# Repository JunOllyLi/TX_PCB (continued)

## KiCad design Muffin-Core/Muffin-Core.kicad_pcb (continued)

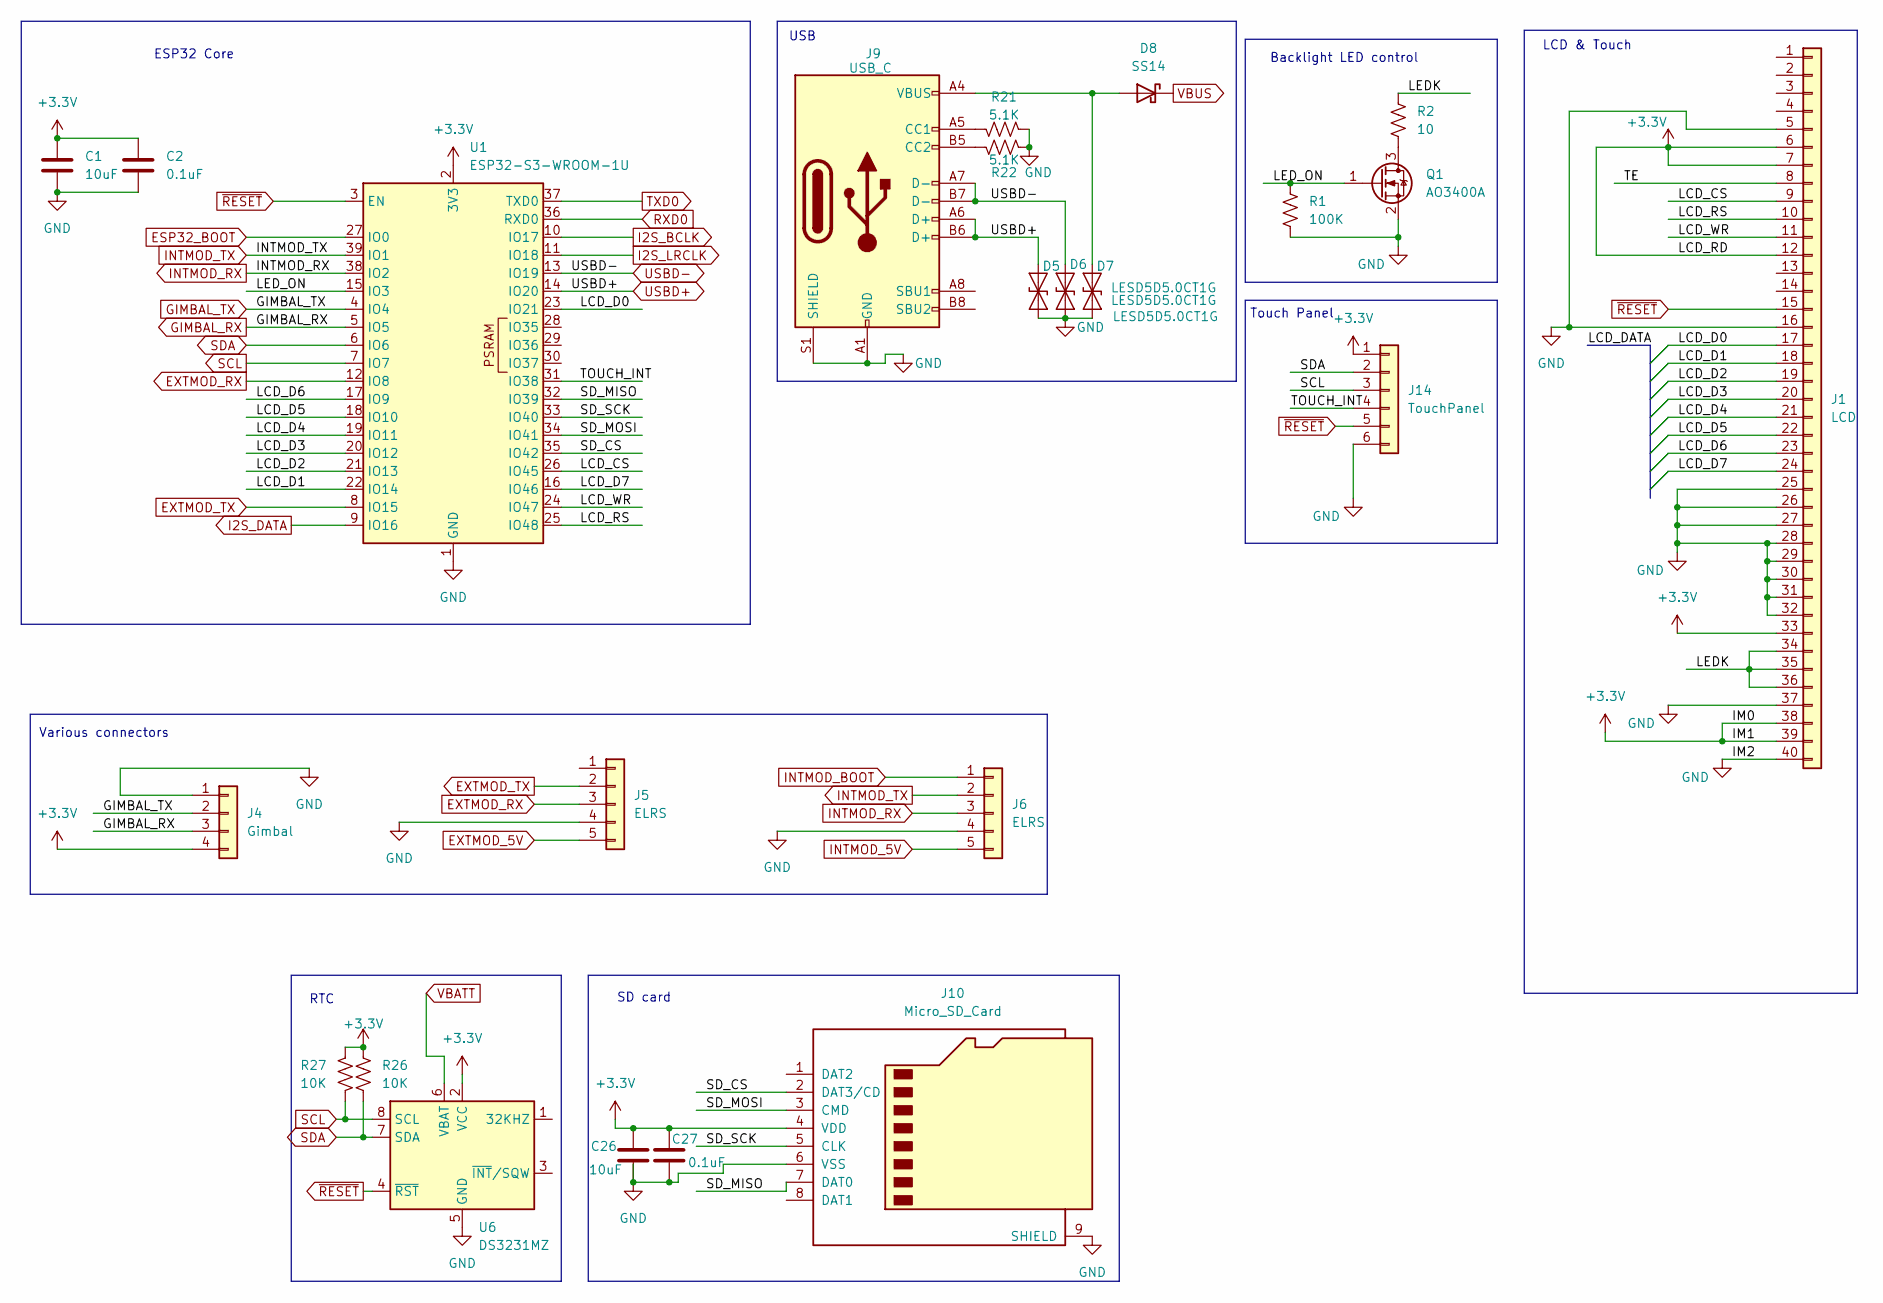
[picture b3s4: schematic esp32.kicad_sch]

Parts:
C1, C26: 10uF; C_0603_1608Metric_Pad1.08x0.95mm_HandSolder
C2, C27: 0.1uF; C_0603_1608Metric_Pad1.08x0.95mm_HandSolder
D5, D6, D7: LESD5D5.0CT1G; D_SOD-523
D8: SS14; D_SMA
J1: LCD; FPC_40PIN_TOP
J4: Gimbal; JST_ZH_B4B-ZR-SM4-TF_1x04-1MP_P1.50mm_Vertical
J5, J6: ELRS; Molex_PicoBlade_53398-0571_1x05-1MP_P1.25mm_Vertical
J9: USB_C; my_USB_C_Receptacle_GCT_USB4105-xx-A_16P_TopMnt_Horizontal
J10: Micro_SD_Card; MicroSD
J14: TouchPanel; FPC_6PIN_BOTTOM
Q1: AO3400A; SOT-23
R1: 100K; R_0603_1608Metric_Pad0.98x0.95mm_HandSolder
R2: 10; R_0603_1608Metric_Pad0.98x0.95mm_HandSolder
R21, R22: 5.1K; R_0603_1608Metric_Pad0.98x0.95mm_HandSolder
R26, R27: 10K; R_0603_1608Metric_Pad0.98x0.95mm_HandSolder
U1: ESP32-S3-WROOM-1U
U6: DS3231MZ; SOIC-8_3.9x4.9mm_P1.27mm

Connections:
+3.3V: C1.1, C2.1, C26.1, C27.1, J1.6, J1.7, J1.12, J1.33, J1.38, J1.39, J4.4, J10.4 (VDD), J14.1, R26.1, R27.1, U1.2 (3V3), U6.2 (VCC); also elsewhere on the board
/ESP32/LCD_CS: J1.9, U1.26 (IO45)
/ESP32/LCD_D0: J1.17, U1.23 (IO21)
/ESP32/LCD_D1: J1.18, U1.22 (IO14)
/ESP32/LCD_D2: J1.19, U1.21 (IO13)
/ESP32/LCD_D3: J1.20, U1.20 (IO12)
/ESP32/LCD_D4: J1.21, U1.19 (IO11)
/ESP32/LCD_D5: J1.22, U1.18 (IO10)
/ESP32/LCD_D6: J1.23, U1.17 (IO9)
/ESP32/LCD_D7: J1.24, U1.16 (IO46)
/ESP32/LCD_RS: J1.10, U1.25 (IO48)
/ESP32/LCD_WR: J1.11, U1.24 (IO47)
/ESP32/LEDK: J1.34, J1.35, J1.36, R2.1
/ESP32/LED_ON: Q1.1 (G), R1.1, U1.15 (IO3)
/ESP32/SD_CS: J10.2 (DAT3/CD), U1.35 (IO42)
/ESP32/SD_MISO: J10.7 (DAT0), U1.32 (IO39)
/ESP32/SD_MOSI: J10.3 (CMD), U1.34 (IO41)
/ESP32/SD_SCK: J10.5 (CLK), U1.33 (IO40)
/ESP32/TE: J1.8
/ESP32/TOUCH_INT: J14.4, U1.31 (IO38)
ESP32_BOOT: U1.27 (IO0); also elsewhere on the board
EXTMOD_5V: J5.5; also elsewhere on the board
EXTMOD_RX: J5.3, U1.12 (IO8); also elsewhere on the board
EXTMOD_TX: J5.2, U1.8 (IO15); also elsewhere on the board
GIMBAL_RX: J4.3, U1.5 (IO5)
GIMBAL_TX: J4.2, U1.4 (IO4)
GND: C1.2, C2.2, C26.2, C27.2, D5.1 (A1), D6.1 (A1), D7.1 (A1), J1.5, J1.16, J1.25, J1.26, J1.27, J1.28, J1.29, J1.30, J1.31, J1.32, J1.37, J1.40, J4.1, J5.4, J6.4, J9.A1 (GND), J9.A12 (GND), J9.B1 (GND), J9.B12 (GND), J9.S1 (SHIELD), J10.6 (VSS), J10.9 (SHIELD), J14.6, Q1.2 (S), R1.2, R21.1, R22.1, U1.1 (GND), U1.40 (GND), U1.41 (GND), U6.5 (GND); also elsewhere on the board
I2S_BCLK: U1.10 (IO17); also elsewhere on the board
I2S_DATA: U1.9 (IO16); also elsewhere on the board
I2S_LRCLK: U1.11 (IO18); also elsewhere on the board
INTMOD_5V: J6.5; also elsewhere on the board
INTMOD_BOOT: J6.1; also elsewhere on the board
INTMOD_RX: J6.3, U1.38 (IO2)
INTMOD_TX: J6.2, U1.39 (IO1)
unnamed: D7.2 (A2), D8.2 (A), J9.A4 (VBUS), J9.A9 (VBUS), J9.B4 (VBUS), J9.B9 (VBUS)
unnamed: J9.A5 (CC1), R21.2
unnamed: J9.B5 (CC2), R22.2
unnamed: Q1.3 (D), R2.2
RXD0: U1.36 (RXD0); also elsewhere on the board
SCL: J14.3, R27.2, U1.7 (IO7), U6.8 (SCL); also elsewhere on the board
SDA: J14.2, R26.2, U1.6 (IO6), U6.7 (SDA); also elsewhere on the board
TXD0: U1.37 (TXD0); also elsewhere on the board
USBD+: D5.2 (A2), J9.A6 (D+), J9.B6 (D+), U1.14 (IO20)
USBD-: D6.2 (A2), J9.A7 (D-), J9.B7 (D-), U1.13 (IO19)
VBATT: U6.6 (VBAT); also elsewhere on the board
VBUS: D8.1 (K); also elsewhere on the board
~RESET: J1.15, J14.5, U1.3 (EN), U6.4 (~RST); also elsewhere on the board

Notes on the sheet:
Backlight LED control
SD card
USB
RTC
Various connectors
Touch Panel
ESP32 Core
LCD & Touch

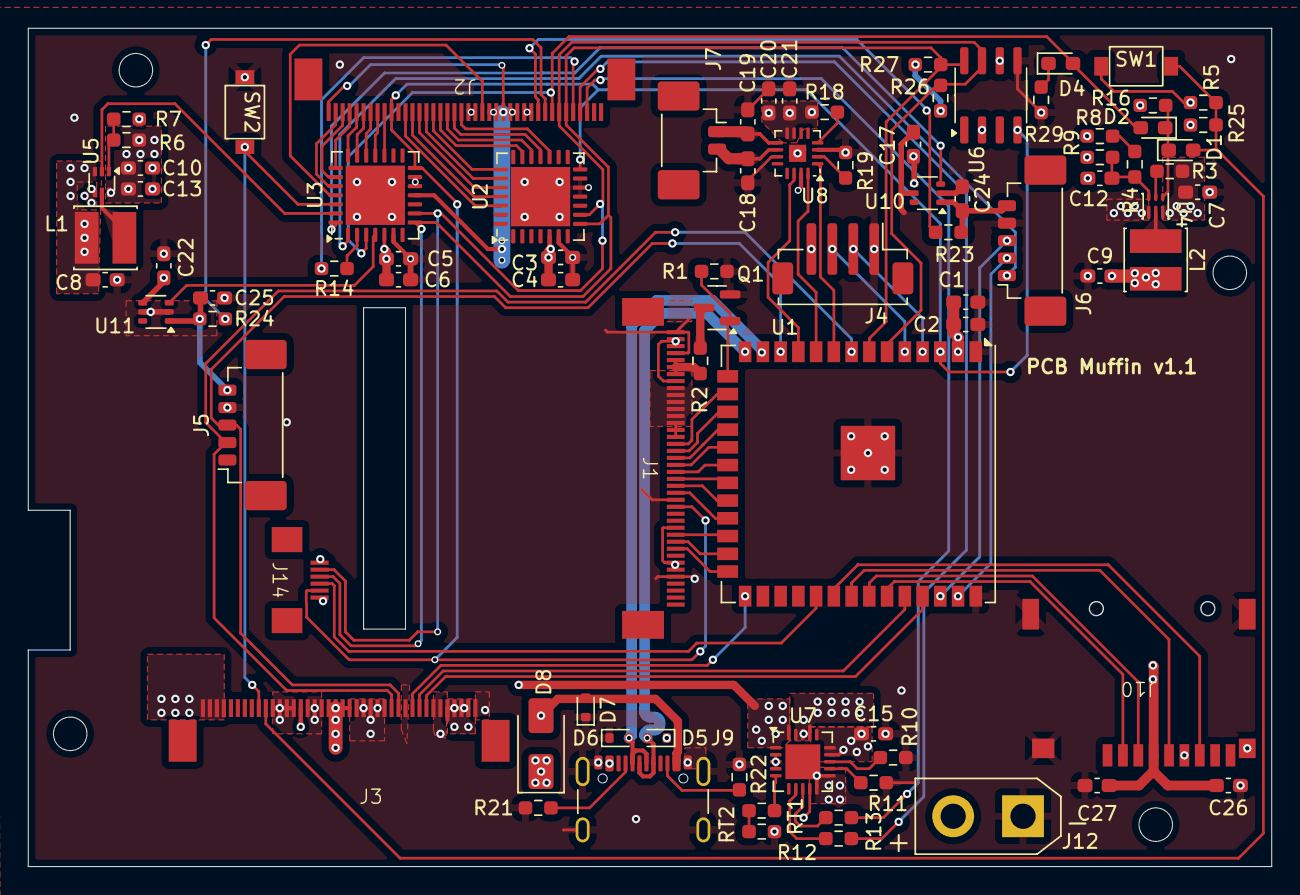
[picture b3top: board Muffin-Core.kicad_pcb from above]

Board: 4 copper layers, 89.0 x 60.0 mm, 83 parts (0 on the bottom side), 96 nets.

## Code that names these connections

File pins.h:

/*
From Kconfig
  LCD D0 - D7: 10, 11, 12, 13, 14, 21, 47, 48
  LCD CS 3
  LCD DC 46
  LCD WR 9

#define I2C_SCL 7
#define I2C_SDA 6

//  MOSI -1
//  MISO -1
//  RESET -1
//  SCLK -1
//  TOUCH CS -1
//  TOUCH IRQ 38
*/

#define TOUCH_IRQ GPIO_NUM_38

#define I2C_MASTER_NUM I2C_NUM_0
#define I2C_0_SCL GPIO_NUM_40
#define I2C_0_SDA GPIO_NUM_39

#define BACKLITE_PIN GPIO_NUM_45

#define USE_RMT -1
#if CONFIG_ESP_CONSOLE_UART_NUM == 0
#define FLYSKY_UART_PORT USE_RMT
#define EXTMOD_UART_PORT UART_NUM_1
#define INTMOD_UART_PORT UART_NUM_2
#else
#define FLYSKY_UART_PORT UART_NUM_0
#define EXTMOD_UART_PORT UART_NUM_1
#define INTMOD_UART_PORT UART_NUM_2
#endif

#define FLYSKY_UART_RX_PIN GPIO_NUM_41  // GIMBLE_TX
#define FLYSKY_UART_TX_PIN GPIO_NUM_42  // GIMBLE_RX

#define INTMOD_ESP_UART_TX GPIO_NUM_2 // INTMOD_RX
#define INTMOD_ESP_UART_RX GPIO_NUM_1 // INTMOD_TX

#define EXTMOD_UART_TX GPIO_NUM_15  // EXTMOD_RX
#define EXTMOD_UART_RX GPIO_NUM_8   // EXTMOD_TX

#define SD_DEDICATED_SPI
#ifdef SD_DEDICATED_SPI
#define SD_SPI_HOST SPI2_HOST
#define SDSPI_CLK GPIO_NUM_5
#define SDSPI_MOSI GPIO_NUM_6
#define SDSPI_MISO GPIO_NUM_4
#endif
#define SDCARD_CS_GPIO GPIO_NUM_7

#define I2S_DOUT GPIO_NUM_16
#define I2S_BCLK GPIO_NUM_17
#define I2S_LRCLK GPIO_NUM_18

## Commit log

2024-05-15 Muffin PCB v1.0
2024-05-18 Readme
2024-08-26 Fix issues found
2024-09-23 V2.0: Combined single board
2024-10-12 PCB 2.1
    Fixed a reversed ZH-socket on the board for Gimbal
2025-02-24 KiCAD 9.0
